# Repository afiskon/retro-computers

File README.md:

# retro-computers

Мои проекты, связанные с ретро-компьютерами

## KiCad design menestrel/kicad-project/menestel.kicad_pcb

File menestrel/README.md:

# Реплика "Менестреля"

Реплика музыкальной приставки "Менестрель" на базе пары чипов КР580ВИ53.

Содержимое каталога:

* kicad-project/ - проект платы, сделанной в KiCad
* enclosure/ - модель корпуса для 3D-печати, сделанная в OpenSCAD
* example/ - простая тестовая программа, компилируемая pdpy11

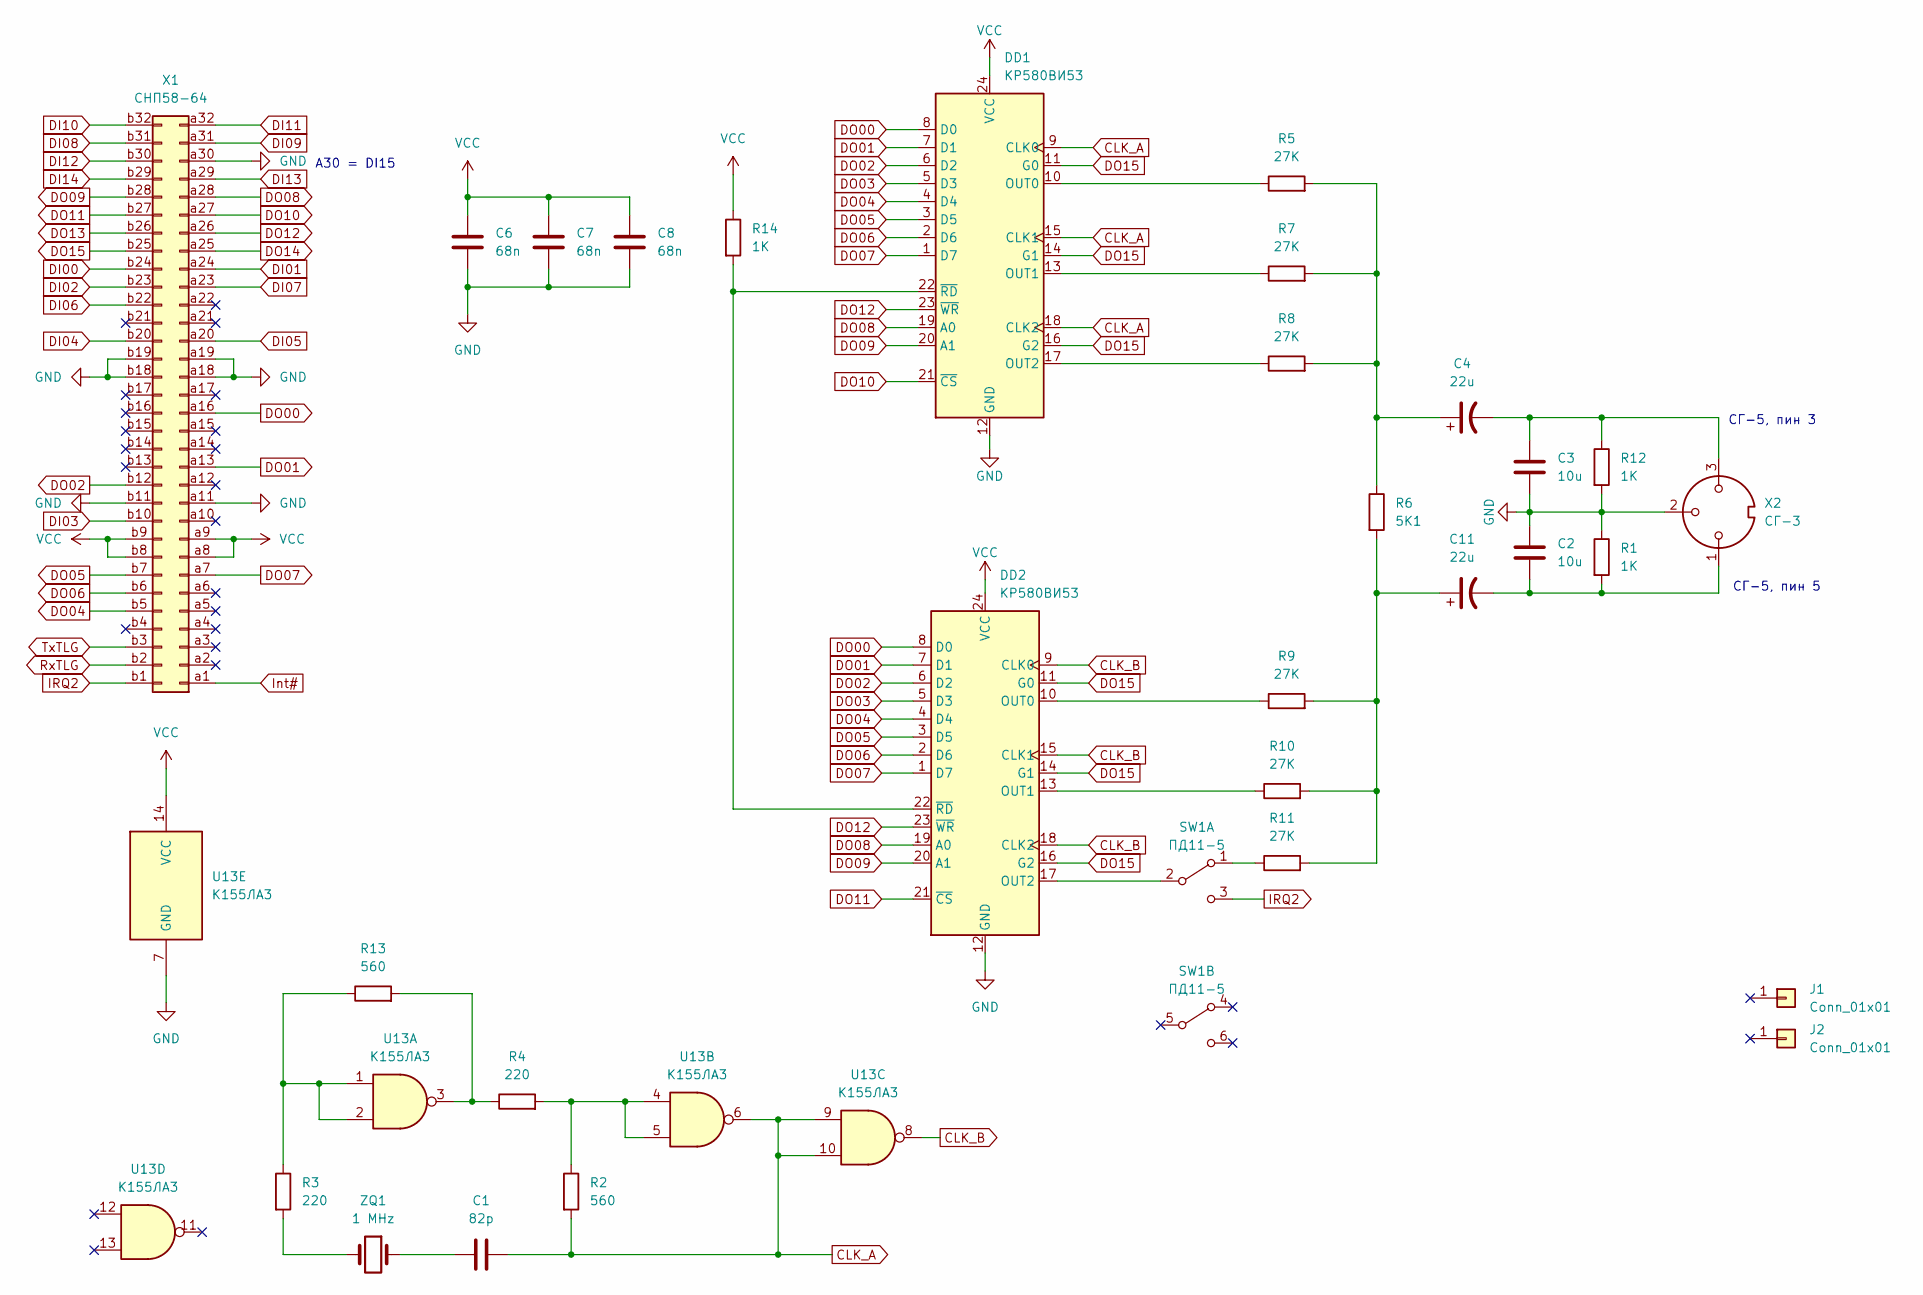
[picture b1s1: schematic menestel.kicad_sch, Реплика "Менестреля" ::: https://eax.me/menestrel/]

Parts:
C1: 82p; C_Disc_D7.5mm_W4.4mm_P5.00mm
C2, C3: 10u; C_Disc_D7.5mm_W4.4mm_P5.00mm
C4, C11: 22u; CP_Radial_D7.5mm_P2.50mm
C6, C7, C8: 68n; C_Disc_D7.5mm_W4.4mm_P5.00mm
DD1, DD2: КР580ВИ53; DIP-24_W15.24mm
J1, J2: Conn_01x01; PinHeader_1x01_P2.54mm_Vertical
R1, R12, R14: 1K; R_Axial_DIN0207_L6.3mm_D2.5mm_P10.16mm_Horizontal
R2, R13: 560; R_Axial_DIN0207_L6.3mm_D2.5mm_P10.16mm_Horizontal
R3, R4: 220; R_Axial_DIN0207_L6.3mm_D2.5mm_P10.16mm_Horizontal
R5, R7, R8, R9, R10, R11: 27K; R_Axial_DIN0207_L6.3mm_D2.5mm_P10.16mm_Horizontal
R6: 5K1; R_Axial_DIN0207_L6.3mm_D2.5mm_P10.16mm_Horizontal
SW1: ПД11-5; SW_PD11_5_DPDT
U13: К155ЛА3; DIP-14_W7.62mm_Socket_LongPads
X1: СНП58-64; SNP58_64_Male_Horizontal_THT
X2: СГ-3; PinHeader_1x03_P2.54mm_Vertical
ZQ1: 1 MHz; Crystal_HC51_Horizontal

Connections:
CLK_A: C1.2, DD1.9 (CLK0), DD1.15 (CLK1), DD1.18 (CLK2), R2.2, U13.6, U13.9, U13.10
CLK_B: DD2.9 (CLK0), DD2.15 (CLK1), DD2.18 (CLK2), U13.8
DI00: X1.b24
DI01: X1.a24
DI02: X1.b23
DI03: X1.b10
DI04: X1.b20
DI05: X1.a20
DI06: X1.b22
DI07: X1.a23
DI08: X1.b31
DI09: X1.a31
DI10: X1.b32
DI11: X1.a32
DI12: X1.b30
DI13: X1.a29
DI14: X1.b29
DO00: DD1.8 (D0), DD2.8 (D0), X1.a16
DO01: DD1.7 (D1), DD2.7 (D1), X1.a13
DO02: DD1.6 (D2), DD2.6 (D2), X1.b12
DO03: DD1.5 (D3), DD2.5 (D3)
DO04: DD1.4 (D4), DD2.4 (D4), X1.b5
DO05: DD1.3 (D5), DD2.3 (D5), X1.b7
DO06: DD1.2 (D6), DD2.2 (D6), X1.b6
DO07: DD1.1 (D7), DD2.1 (D7), X1.a7
DO08: DD1.19 (A0), DD2.19 (A0), X1.a28
DO09: DD1.20 (A1), DD2.20 (A1), X1.b28
DO10: DD1.21 (~CS), X1.a27
DO11: DD2.21 (~CS), X1.b27
DO12: DD1.23 (~WR), DD2.23 (~WR), X1.a26
DO13: X1.b26
DO14: X1.a25
DO15: DD1.11 (G0), DD1.14 (G1), DD1.16 (G2), DD2.11 (G0), DD2.14 (G1), DD2.16 (G2), X1.b25
GND: C2.1, C3.2, C6.2, C7.2, C8.2, DD1.12 (GND), DD2.12 (GND), R1.1, R12.2, U13.7 (GND), X1.a11, X1.a18, X1.a19, X1.a30, X1.b11, X1.b18, X1.b19, X2.2
IRQ2: SW1.3 (C), X1.b1
Int#: X1.a1
unnamed: C1.1, ZQ1.1
unnamed: C3.1, C4.2, R12.1, X2.3
unnamed: C4.1, R5.2, R6.1, R7.2, R8.2
unnamed: C11.1, R6.2, R9.2, R10.2, R11.2
unnamed: C2.2, C11.2, R1.2, X2.1
unnamed: DD1.10 (OUT0), R5.1
unnamed: DD1.13 (OUT1), R7.1
unnamed: DD1.17 (OUT2), R8.1
unnamed: DD1.22 (~RD), DD2.22 (~RD), R14.2
unnamed: DD2.10 (OUT0), R9.1
unnamed: DD2.13 (OUT1), R10.1
unnamed: DD2.17 (OUT2), SW1.2 (B)
unnamed: R2.1, R4.2, U13.4, U13.5
unnamed: R3.2, ZQ1.2
unnamed: R3.1, R13.1, U13.1, U13.2
unnamed: R4.1, R13.2, U13.3
unnamed: R11.1, SW1.1 (A)
RxTLG: X1.b2
TxTLG: X1.b3
VCC: C6.1, C7.1, C8.1, DD1.24 (VCC), DD2.24 (VCC), R14.1, U13.14 (VCC), X1.a8, X1.a9, X1.b8, X1.b9

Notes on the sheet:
СГ-5, пин 3
СГ-5, пин 5
A30 = DI15

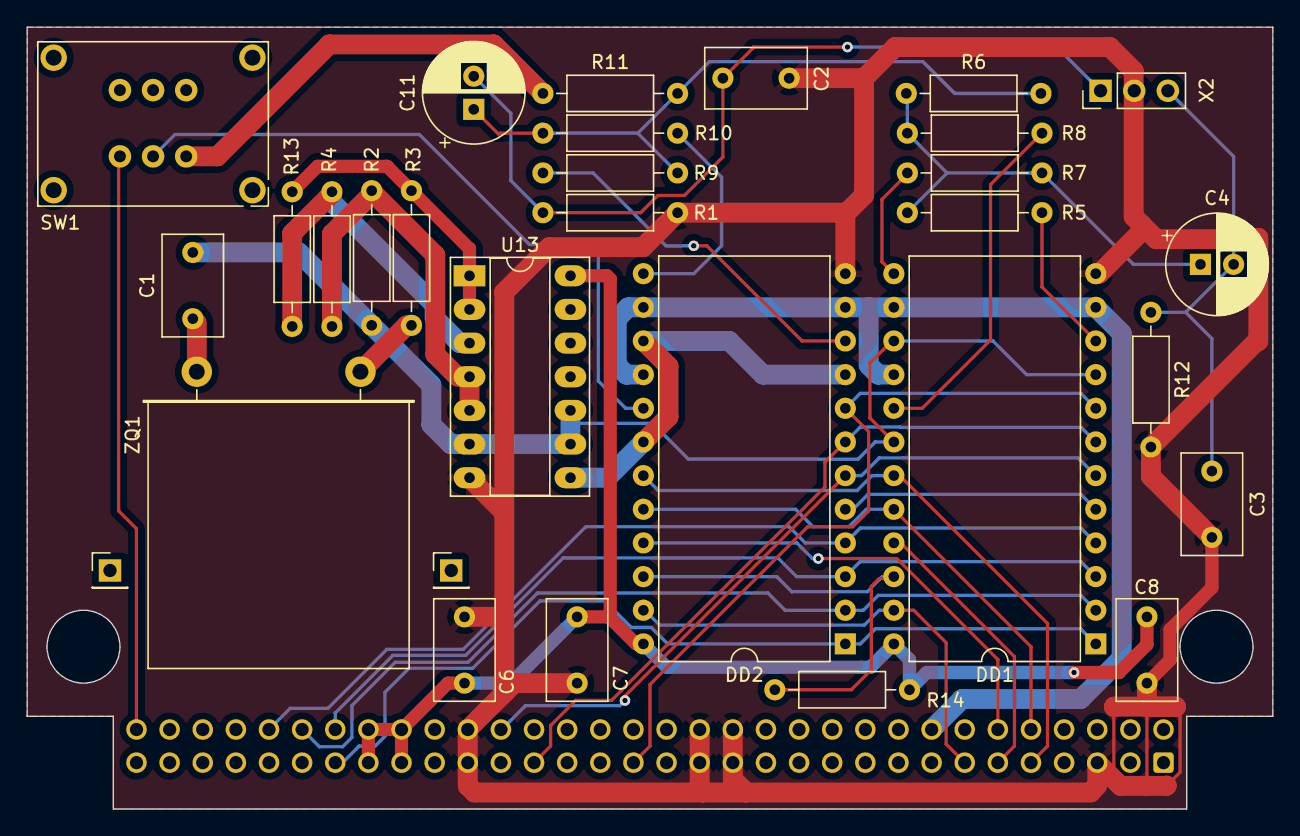
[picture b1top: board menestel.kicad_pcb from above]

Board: 2 copper layers, 94.0 x 59.0 mm, 31 parts (0 on the bottom side), 36 nets.

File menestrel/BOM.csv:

Reference(s),Qty,Value,Footprint
C1,1,82p,Capacitor_THT:C_Disc_D7.5mm_W4.4mm_P5.00mm
"C2, C3",2,10u,Capacitor_THT:C_Disc_D7.5mm_W4.4mm_P5.00mm
"C4, C11",2,22u,Capacitor_THT:CP_Radial_D7.5mm_P2.50mm
"C6, C7, C8",3,68n,Capacitor_THT:C_Disc_D7.5mm_W4.4mm_P5.00mm
"DD1, DD2",2,КР580ВИ53,Package_DIP:DIP-24_W15.24mm
"R1, R12, R14",3,1K,Resistor_THT:R_Axial_DIN0207_L6.3mm_D2.5mm_P10.16mm_Horizontal
"R2, R13",2,560,Resistor_THT:R_Axial_DIN0207_L6.3mm_D2.5mm_P10.16mm_Horizontal
"R3, R4",2,220,Resistor_THT:R_Axial_DIN0207_L6.3mm_D2.5mm_P10.16mm_Horizontal
"R5, R7, R8, R9, R10, R11",6,27K,Resistor_THT:R_Axial_DIN0207_L6.3mm_D2.5mm_P10.16mm_Horizontal
R6,1,5K1,Resistor_THT:R_Axial_DIN0207_L6.3mm_D2.5mm_P10.16mm_Horizontal
SW1,1,ПД11-5,My_Library:SW_PD11_5_DPDT
U13,1,К155ЛА3,Package_DIP:DIP-14_W7.62mm_Socket_LongPads
X1,1,СНП58-64,My_Library:SNP58_64_Male_Horizontal_THT
X2,1,СГ-3,Connector_PinHeader_2.54mm:PinHeader_1x03_P2.54mm_Vertical
ZQ1,1,1 MHz,Crystal:Crystal_HC51_Horizontal

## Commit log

2023-06-18 Добавлена реплика "Менестреля"
2023-06-23 Правка мелких косяков Менестреля rev1
2023-06-23 Радиус крепежный отверстий "Менестреля" исправлен с 2.5 на 2.75 мм
2023-06-23 Схема и gerber-файлы Менестреля rev2
2023-06-23 Поправлен мелкий косяк в схеме "Менестреля"
2023-06-24 Добавлена модель корпуса "Менестреля"
2023-06-25 Менестрель: добавлен STL верхней крышки без дырок
2023-06-25 Менестрель: исправлены номиналы C2 и C3 (u10 = 0.1 мкФ, не 10 мкФ)
2023-06-25 Менестрель: добавлена простая тестовая программа
2023-06-25 Менестрель: мелкие правки README
2023-06-25 Добавлен .gitignore
2023-06-25 Менестрель: поправлены отступы в тестовой программе
2023-07-04 Добавлен Tencolors: программа выводящая десять цветов
2024-09-28 Переименовал репозиторий, завел каталог bk001x/
2024-09-28 Корневой README
2024-09-28 Перенес asm80.py из форка github.com/afiskon/suite8080
2024-09-28 Minor changes
2024-09-28 Перенес мелкие наработки для Искры из sandbox-а
2024-09-28 Перенес "Змейку" для Искры из sandbox-а
2024-09-28 Добавил README для змейки
2024-09-29 asm80: "anonymous labels" is the proper term, not "local labels"
2024-09-29 asm80: update README
2024-09-29 lvt2wav: update README
2024-09-30 Clean-up assets.xcf
2024-09-30 Add zmejka.lvt
2024-09-30 Добавил ссылки на статьи о БК и Искре
2024-09-30 Змейка для Искры: добавил ссылки на статью и демо
2024-10-01 Начинать .lvt с LVOV/2.0/ для совместимости с эмуляторами
2024-10-06 zmejka: заменить табы на пробелы чтобы код лучше читался на github
2026-04-17 Change computer link in README.md
    Updated the computer link to a new URL.
2026-04-17 Update link for BK-0010-01 details
